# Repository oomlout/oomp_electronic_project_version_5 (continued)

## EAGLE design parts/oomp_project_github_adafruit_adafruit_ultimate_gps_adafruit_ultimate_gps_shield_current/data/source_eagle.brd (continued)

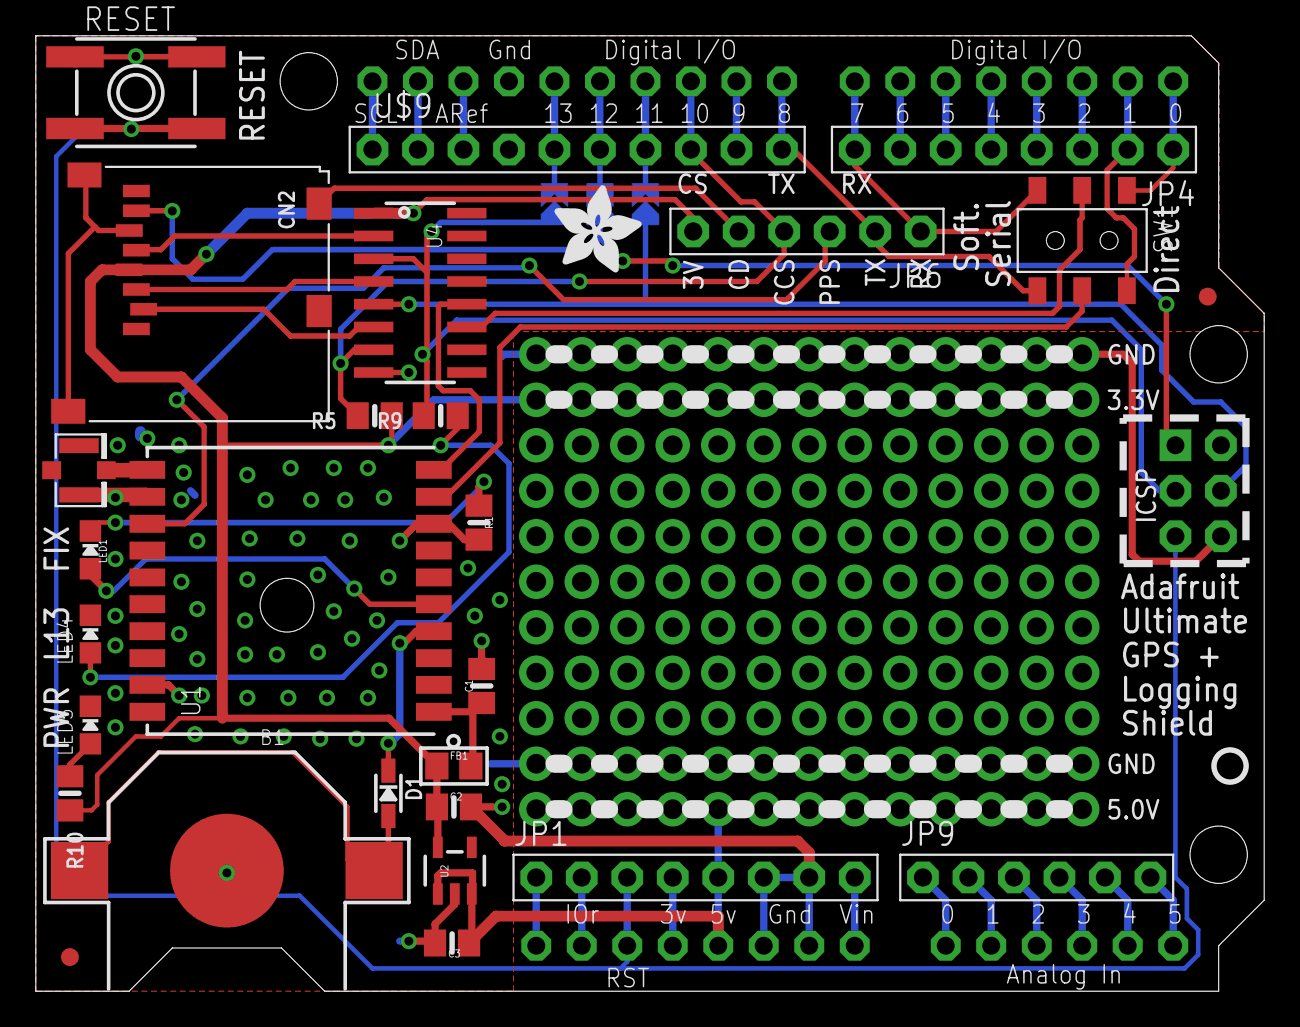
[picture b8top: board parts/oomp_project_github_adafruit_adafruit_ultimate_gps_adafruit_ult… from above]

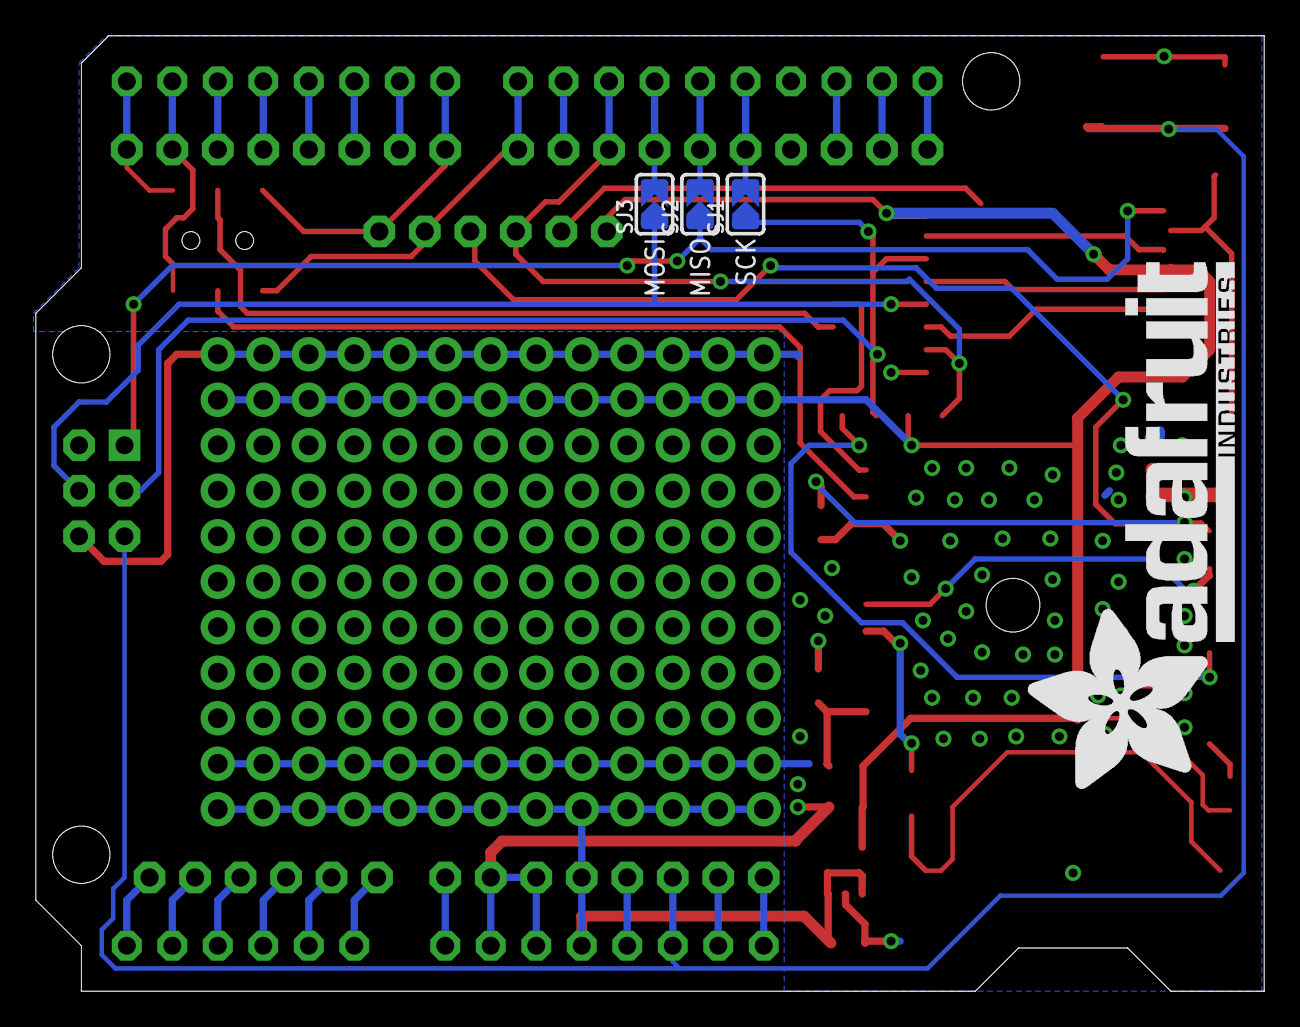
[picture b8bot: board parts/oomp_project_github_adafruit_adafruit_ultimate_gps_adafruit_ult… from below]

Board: 2 copper layers, 68.6 x 53.3 mm, 34 parts (4 on the bottom side), 50 nets.

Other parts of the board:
U$13: ADAFRUIT_5MM
U$15: ADAFRUIT_TEXT_30MM
U$16: PCBFEAT-REV-040

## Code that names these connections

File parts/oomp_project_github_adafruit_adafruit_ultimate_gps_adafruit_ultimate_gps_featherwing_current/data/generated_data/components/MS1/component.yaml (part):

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      no_connect: false
      connected_to: []
    - number: '19'
      name: GPIO5
      electrical_type: bidirectional
      graphic_style: line
      local_position:
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      no_connect: false
      connected_to: []
    - number: '20'
      name: GPIO6
      electrical_type: bidirectional
      graphic_style: line
      local_position:
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      no_connect: false
      connected_to: []
    - number: '23'
      name: GPIO11
      electrical_type: bidirectional
      graphic_style: line
      local_position:
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        pin_number: '5'
        pin_name: '5'
    - number: '24'
      name: GPIO12
      electrical_type: bidirectional
      graphic_style: line
      local_position:
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        pin_number: '4'
        pin_name: '4'
    - number: '25'
      name: GPIO13
      electrical_type: bidirectional
      graphic_style: line
      local_position:
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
